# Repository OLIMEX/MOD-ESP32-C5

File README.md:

# MOD-ESP32-C5
ESP32-C5 dual band 2.4/5Ghz WiFi6 UEXT module

https://www.olimex.com/Products/IoT/ESP32-C5/MOD-ESP32-C5/open-source-hardware

## Licensee
* Hardware is released under CERN Open Hardware Licence Version 2 - Strongly Reciprocal
* Software is released under MIT Licensee
* Documentation is released under CC BY-SA 4.0

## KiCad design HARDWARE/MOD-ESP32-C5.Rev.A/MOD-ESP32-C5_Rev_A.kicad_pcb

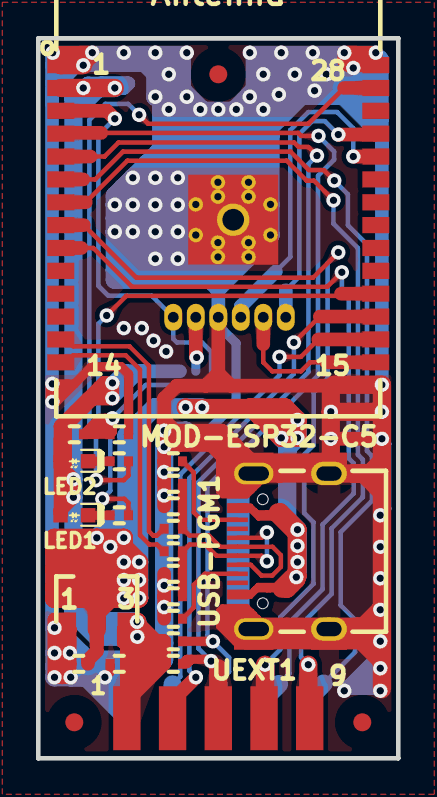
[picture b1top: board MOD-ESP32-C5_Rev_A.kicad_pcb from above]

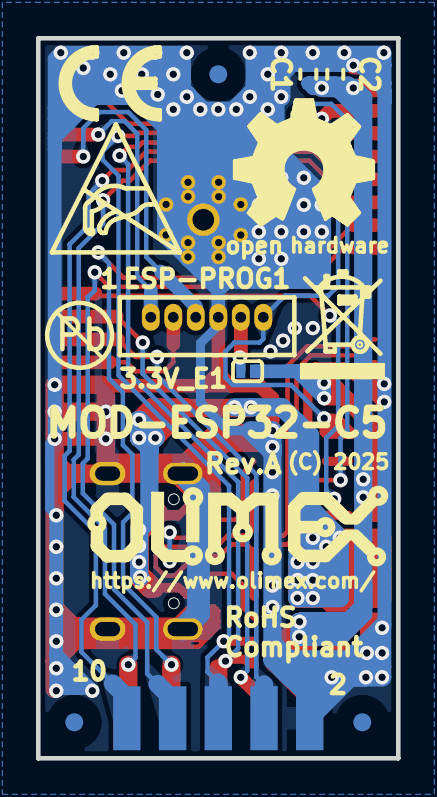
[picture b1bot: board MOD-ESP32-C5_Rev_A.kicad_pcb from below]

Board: 2 copper layers, 20.0 x 40.0 mm, 38 parts (13 on the bottom side), 26 nets.

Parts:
3.3V_E1: Opened; SJ_1_SMALLER
C1: NA(10uF/6.3V/20%/X5R/C0402); C_0402_5MIL_DWS
C2: NA(100nF/10V/20%/X5R/C0402); C_0402_5MIL_DWS
C3: 1uF/6.3V/10%/X5R/C0402; C_0402_5MIL_DWS
C4, C5: NA(150pF/50V/2%/NP0/C0402); C_0402_5MIL_DWS
C6, C7: 10uF/6.3V/20%/X5R/C0402; C_0402_5MIL_DWS
ESP-PROG1: NA(WU06S); WU06S
FID1, FID2, FID5, FID6: Fiducial; Fiducial1x3
FID3, FID4: Fiducial; Fiducial1x3_Paste
LED1: LED/Green/0603; LED_0603_KA
LED2: LED/Red/0603; LED_0603_KA
Logo_OLIMEX_TB: Logo_OLIMEX_TB
R1, R2: 5.1k/1%/R0402; R_0402_5MIL_DWS
R3: 10k/R0402; R_0402_5MIL_DWS
R4, R5: 33R/R0402; R_0402_5MIL_DWS
R6, R7: 2.2k/R0402; R_0402_5MIL_DWS
R8, R9: NA(10k/R0402); R_0402_5MIL_DWS
Sign_Antistatic: Sign_Antistatic
Sign_CE: CE_Sign
Sign_OSHW_8x8: Sign_OSHW_8x8
Sign_PB-Free: Sign_PB-Free
Sign_RecycleBin_1: Sign_RecycleBin_1
TVS1, TVS2: GG0402052R542P; D_0402_5MIL_DWS
U1: ESP32-C5-WROOM-1-N8R4; ESP32-C5-WROOM-1-N**4-UNIVERSAL_MODULE
UEXT1: FK-DK-2X05-LF(IDC-10S_PCB); FK-DK-2X05-LF(IDC-10S_PCB)-SMD
USB-PGM1: USB-C-16P-F(A40-00119-A52-12); USB2.0_TYPE-C(A40-00119-A52-12)_Paste
VR1: WL9005P3-33(SOT89-3); SOT89-3

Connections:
+3.3V: 3.3V_E1.2, C1.2, C2.1, C7.1, LED1.2 (A), LED2.2 (A), R3.2, R8.1, R9.2, U1.2 (3V3), UEXT1.1, VR1.3 (VOUT)
+5V_USB: C6.1, USB-PGM1.A4 (VBUS), USB-PGM1.A9 (VBUS), USB-PGM1.B4 (VBUS), USB-PGM1.B9 (VBUS), VR1.2 (VIN)
/ESP_EN: C3.2, ESP-PROG1.6, R3.1, U1.3 (EN)
/GPIO0\SPI2_CS: U1.6 (IO0/GPIO0/XTAL_32K_P/LP_GPIO0/LP_UART_D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), UEXT1.10
/GPIO1\SPI2_CLK: U1.7 (IO1/GPIO1/XTAL_32K_N/LP_GPIO1/LP_UART_D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), UEXT1.9
/GPIO2\LP_I2C_SDA\I2C_SDA: R9.1, U1.4 (IO2/MTMS/GPIO2/LP_GPIO2/LP_UART_RTSN/LP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), UEXT1.6
/GPIO3\LP_I2C_SCL\I2C_SCL: R8.2, U1.5 (IO3/MTDI/GPIO3/LP_GPIO3/LP_UART_CTSN/LP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), UEXT1.5
/GPIO4\LP_UART_RXD\U1RXD: U1.17 (IO4/MTCK/GPIO4/LP_GPIO4/LP_UART_RXD/ADC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), UEXT1.3
/GPIO5\LP_UART_TXD\U1TXD: U1.16 (IO5/MTDO/GPIO5/LP_GPIO5/LP_UART_TXD/ADC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), UEXT1.4
/GPIO6\SPI2_MISO: U1.8 (IO6/GPIO6/LP_GPIO6/ADC1_CH5/FSPICLK), UEXT1.7
/GPIO7\SPI2_MOSI: U1.9 (IO7/GPIO7/LP_GPIO7/FSPID/SDIO_DATA1), UEXT1.8
/GPIO11\U0TXD: ESP-PROG1.1, U1.25 (IO11/U0TXD/GPIO11)
/GPIO12\U0RXD: ESP-PROG1.3, U1.24 (IO12/U0RXD/GPIO12)
/GPIO26\USER_LED2: R7.2, U1.27 (IO26/GPIO26)
/GPIO27\USER_LED1: R6.2, U1.18 (IO27/GPIO27)
/GPIO28\BOOT: ESP-PROG1.2, U1.15 (IO28/GPIO28)
/USB_D+: C5.1, R5.2, TVS1.1 (IO1), USB-PGM1.A6 (DP1), USB-PGM1.B6 (DP2)
/USB_D-: C4.1, R4.1, TVS2.1 (IO1), USB-PGM1.A7 (DN1), USB-PGM1.B7 (DN2)
/USB_DN: R4.2, U1.13 (IO13/GPIO13/USB_D-/SDIO_DATA3)
/USB_DP: R5.1, U1.14 (IO14/GPIO14/USB_D+/SDIO_DATA2)
GND: C1.1, C2.2, C3.1, C4.2, C5.2, C6.2, C7.2, ESP-PROG1.4, R1.1, R2.1, TVS1.2 (IO2), TVS2.2 (IO2), U1.1 (GND), U1.28 (GND), U1.29 (EPAD), UEXT1.2, USB-PGM1.0 (SHELL), USB-PGM1.A1 (GND), USB-PGM1.A12 (GND), USB-PGM1.B1 (GND), USB-PGM1.B12 (GND), VR1.1 (GND)
unnamed: 3.3V_E1.1, ESP-PROG1.5
unnamed: LED1.1 (K), R6.1
unnamed: LED2.1 (K), R7.1
unnamed: R2.2, USB-PGM1.A5 (CC1)
unnamed: R1.2, USB-PGM1.B5 (CC2)

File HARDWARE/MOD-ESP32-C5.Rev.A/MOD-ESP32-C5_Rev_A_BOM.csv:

Quantity,Value,Footprint,Reference
1,1uF/6.3V/10%/X5R/C0402,C_0402_5MIL_DWS,C3
2,10uF/6.3V/20%/X5R/C0402,C_0402_5MIL_DWS,"C6, C7"
1,LED/Green/0603,LED_0603_KA,LED1
1,LED/Red/0603,LED_0603_KA,LED2
2,5.1k/1%/R0402,R_0402_5MIL_DWS,"R1, R2"
1,10k/R0402,R_0402_5MIL_DWS,R3
2,33R/R0402,R_0402_5MIL_DWS,"R4, R5"
2,2.2k/R0402,R_0402_5MIL_DWS,"R6, R7"
2,GG0402052R542P,D_0402_5MIL_DWS,"TVS1, TVS2"
1,ESP32-C5-WROOM-1-N8R4,ESP32-C5-WROOM-1-N**4-UNIVERSAL_MODULE,U1
1,FK-DK-2X05-LF(IDC-10S_PCB),FK-DK-2X05-LF(IDC-10S_PCB)-SMD,UEXT1
1,USB-C-16P-F(A40-00119-A52-12),USB2.0_TYPE-C(A40-00119-A52-12)_Paste,USB-PGM1
1,WL9005P3-33(SOT89-3),SOT89-3,VR1

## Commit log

2025-12-03 initial upload
2025-12-04 add user manual
2025-12-11 Update
    IDF demo
2026-05-14 Update
    Added WIFI functionality firmware and demos with Olimexino-2560 for Arduino IDE
2026-05-14 Update
    Py scripts for Olinuxino boards

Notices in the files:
HARDWARE/MOD-ESP32-C5.Rev.A/MOD-ESP32-C5_Rev_A.kicad_pcb:
(C) 2025
